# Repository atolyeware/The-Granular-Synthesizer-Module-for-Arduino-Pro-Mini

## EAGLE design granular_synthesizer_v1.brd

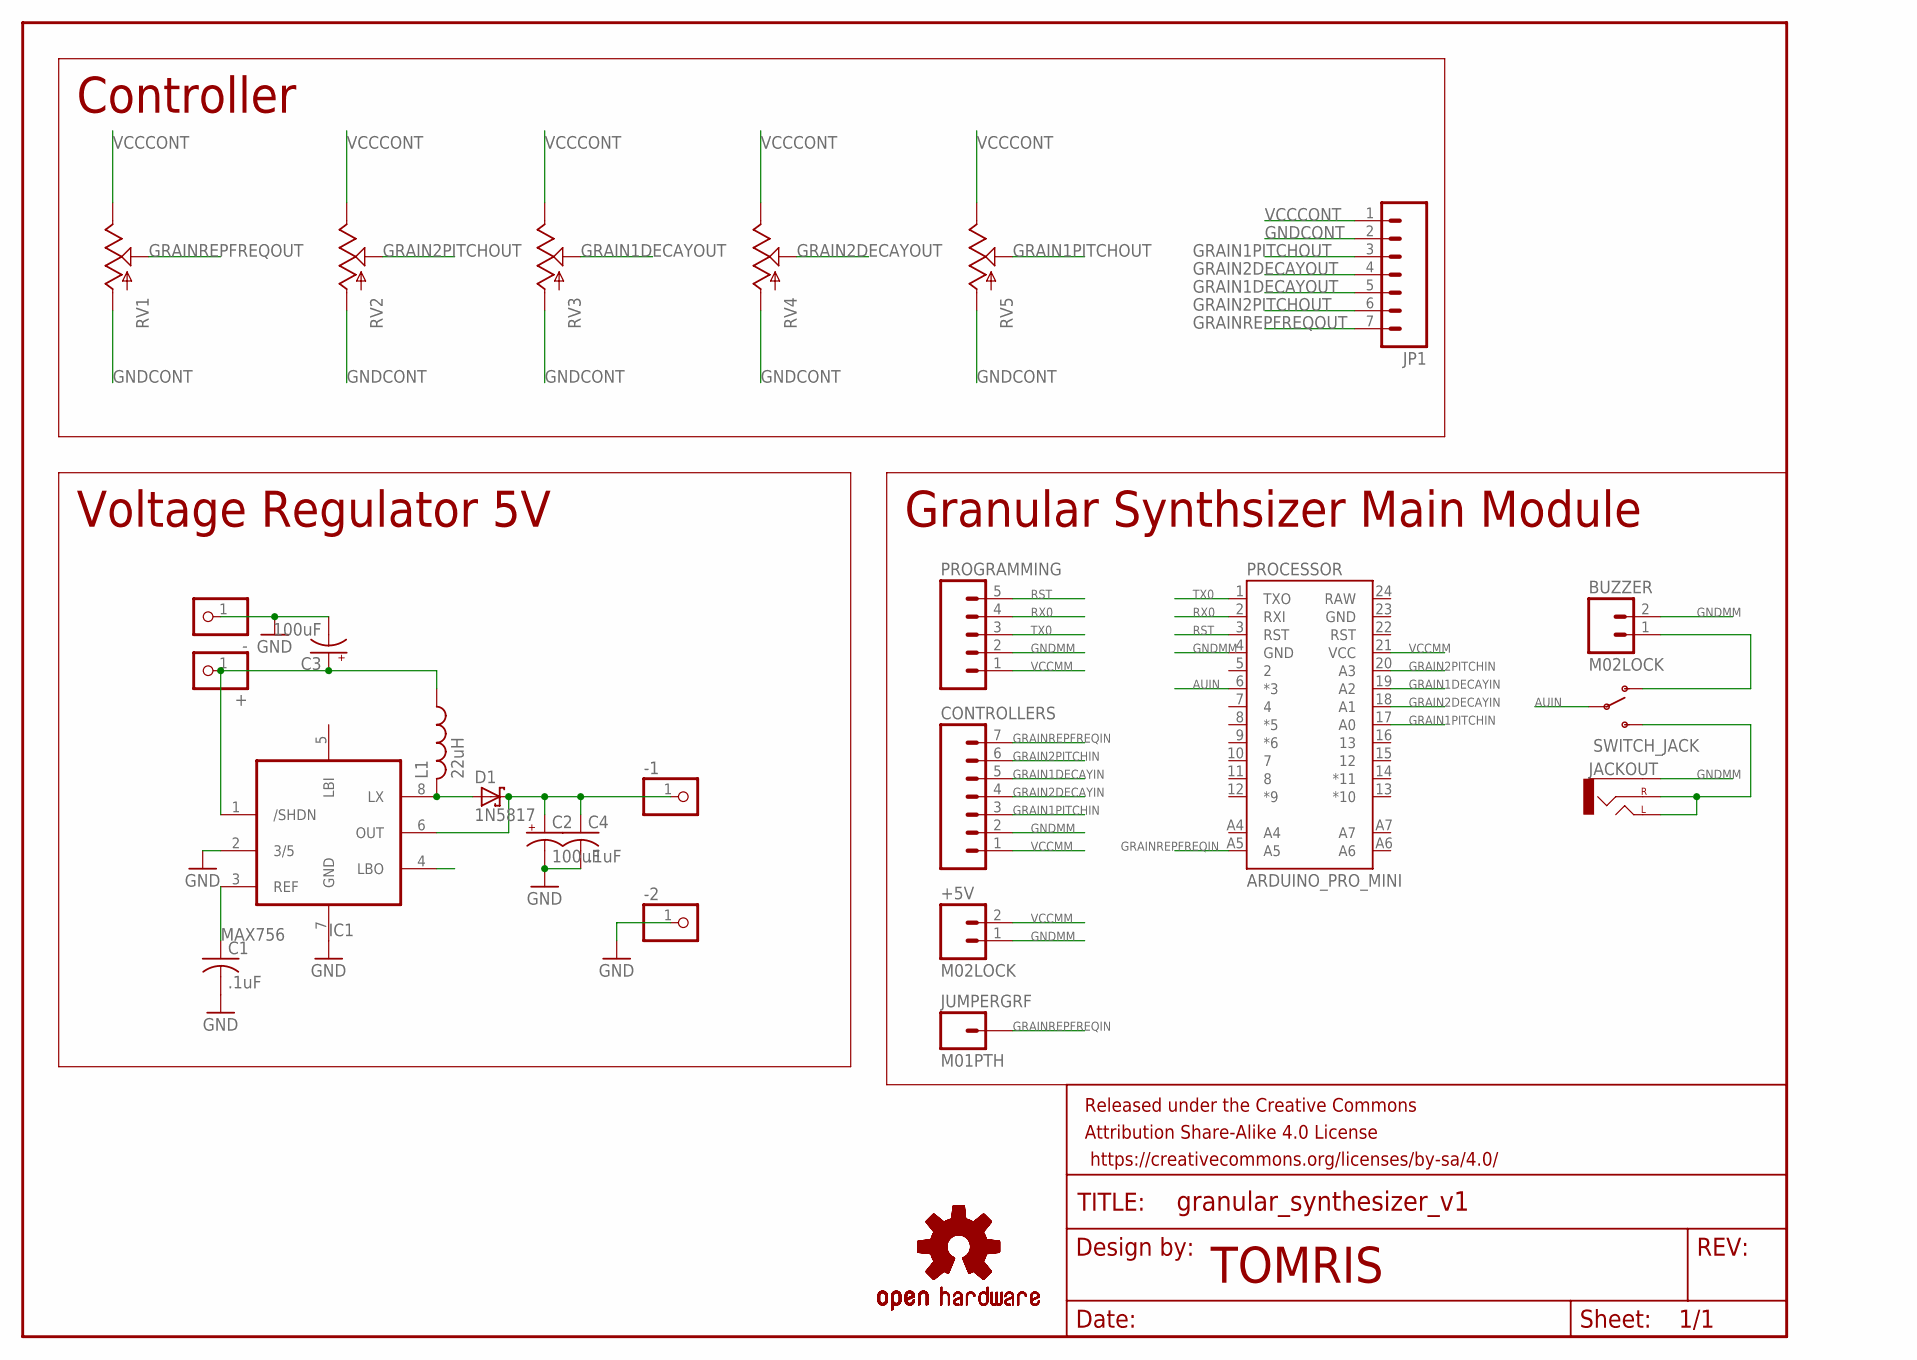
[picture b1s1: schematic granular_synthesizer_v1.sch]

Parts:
+: PINHD-1X1; 1X01
+5V: M02LOCK; 1X02_LOCK
-, -1, -2: PINHD-1X1; 1X01
BUZZER: M02LOCK; 1X02_LOCK
C1, C4: .1uF; C025-024X044
C2, C3: 100uF; E2,5-5
CONTROLLERS: M07; 1X07
D1: 1N5817; DO41-10
FRAME1: FRAME-LETTER; CREATIVE_COMMONS
IC1: MAX756; DIL08
JACKOUT: AUDIO-JACK2.5MM; STEREOJACK2.5MM_STEREOJACK2.5MM
JP1: M07; 1X07
JUMPERGRF: M01PTH; 1X01
L1: 22uH; 2747
LOGO1, LOGO2, LOGO3: OSHW-LOGOM; OSHW-LOGO-M
PROCESSOR: ARDUINO_PRO_MINI
PROGRAMMING: M05LOCK; 1X05_LOCK
RV1, RV2, RV3, RV4, RV5: POTMAM; POT_MAMMOTH
SWITCH_JACK: SWITCH-SPDTPTH; SWITCH-SPDT

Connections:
AUIN: PROCESSOR.6 (*3), SWITCH_JACK.2
GND: -.1, -2.1, C1.2, C2.-, C3.-, C4.2, IC1.2 (3/5), IC1.7 (GND)
GNDCONT: JP1.2, RV1.P$2 (A), RV2.P$2 (A), RV3.P$2 (A), RV4.P$2 (A), RV5.P$2 (A)
GNDMM: +5V.1, BUZZER.2, CONTROLLERS.2, JACKOUT.RING1 (SLEEVE), PROCESSOR.4 (GND), PROGRAMMING.2
GRAIN1DECAYIN: CONTROLLERS.5, PROCESSOR.19 (A2)
GRAIN1DECAYOUT: JP1.5, RV3.P$1 (S)
GRAIN1PITCHIN: CONTROLLERS.3, PROCESSOR.17 (A0)
GRAIN1PITCHOUT: JP1.3, RV5.P$1 (S)
GRAIN2DECAYIN: CONTROLLERS.4, PROCESSOR.18 (A1)
GRAIN2DECAYOUT: JP1.4, RV4.P$1 (S)
GRAIN2PITCHIN: CONTROLLERS.6, PROCESSOR.20 (A3)
GRAIN2PITCHOUT: JP1.6, RV2.P$1 (S)
GRAINREPFREQIN: CONTROLLERS.7, JUMPERGRF.1, PROCESSOR.A5
GRAINREPFREQOUT: JP1.7, RV1.P$1 (S)
unnamed: JACKOUT.SHIELD (LEFT), JACKOUT.TIP (RIGHT), SWITCH_JACK.3 (S)
unnamed: C1.1, IC1.3 (REF)
unnamed: +.1, C3.+, IC1.1 (/SHDN), L1.P$1 (1)
unnamed: BUZZER.1, SWITCH_JACK.1 (O)
unnamed: D1.A, IC1.8 (LX), L1.P$2 (2)
unnamed: -1.1, C2.+, C4.1, D1.C, IC1.6 (OUT)
RST: PROCESSOR.3 (RST), PROGRAMMING.5
RX0: PROCESSOR.2 (RXI), PROGRAMMING.4
TX0: PROCESSOR.1 (TXO), PROGRAMMING.3
VCCCONT: JP1.1, RV1.P$3 (E), RV2.P$3 (E), RV3.P$3 (E), RV4.P$3 (E), RV5.P$3 (E)
VCCMM: +5V.2, CONTROLLERS.1, PROCESSOR.21 (VCC), PROGRAMMING.1

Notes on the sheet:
TOMRIS
Granular Synthsizer Main Module
Controller
Voltage Regulator 5V

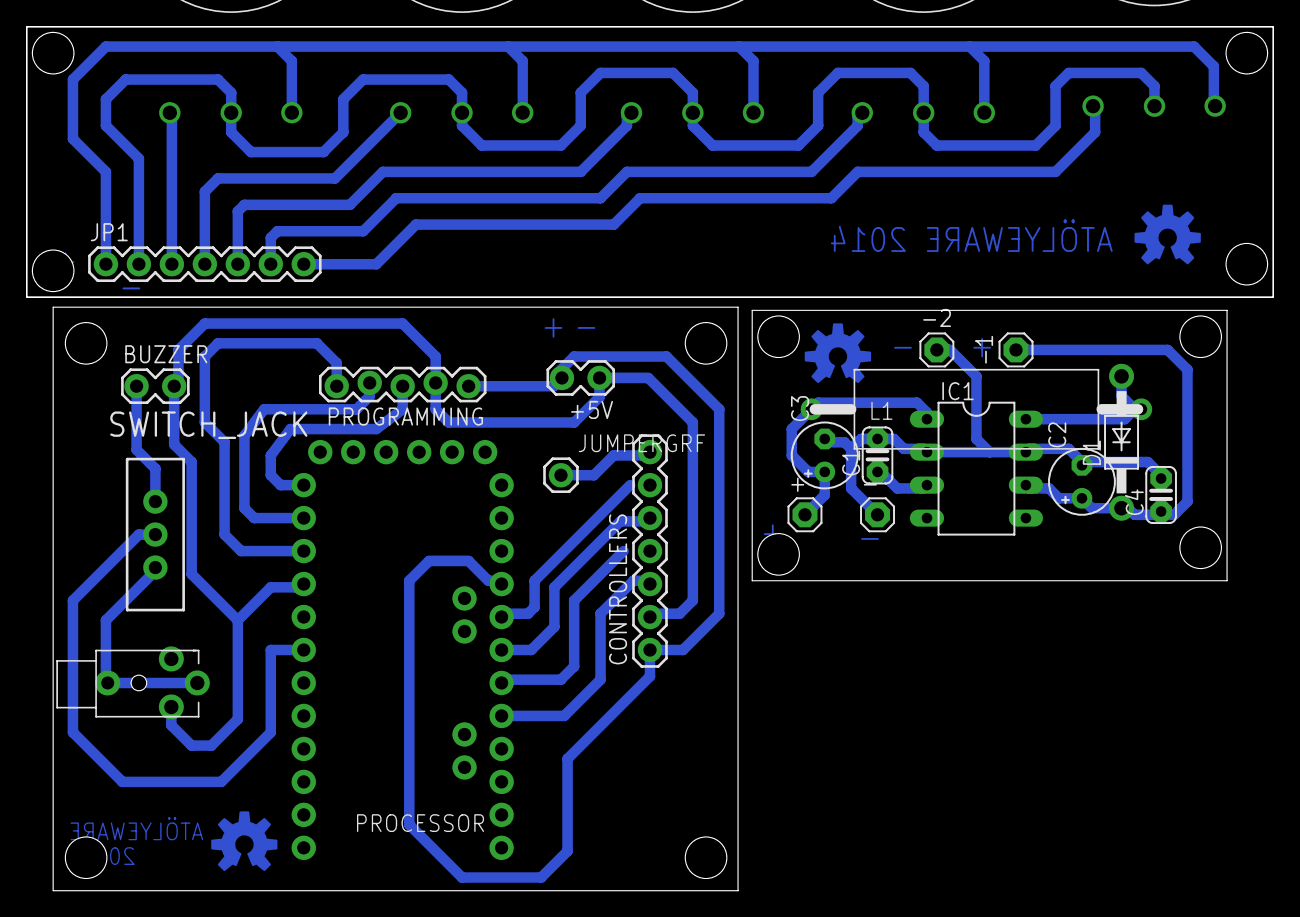
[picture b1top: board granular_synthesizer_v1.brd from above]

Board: 2 copper layers, 96.0 x 66.5 mm, 29 parts (0 on the bottom side), 25 nets.

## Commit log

2016-08-26 :confetti_ball: Added .gitattributes & .gitignore files
2016-08-26 adding *.brd, *.sch files
    adding files

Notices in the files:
parts and their libraries:
SparkFun-Connectors: Licensing: Creative Commons ShareAlike 4.0 International - https://creativecommons.org/licenses/by-sa/4.0
SparkFun-Aesthetics: Released under the Creative Commons Attribution Share-Alike 4.0 License
SparkFun-Aesthetics: https://creativecommons.org/licenses/by-sa/4.0
